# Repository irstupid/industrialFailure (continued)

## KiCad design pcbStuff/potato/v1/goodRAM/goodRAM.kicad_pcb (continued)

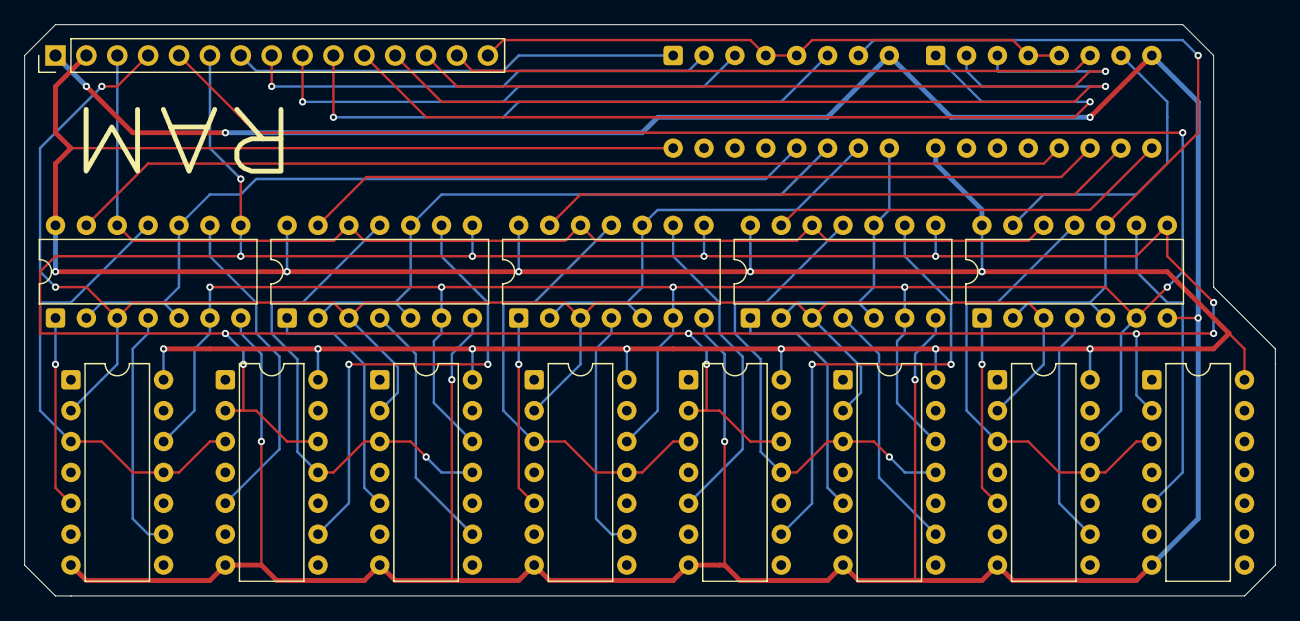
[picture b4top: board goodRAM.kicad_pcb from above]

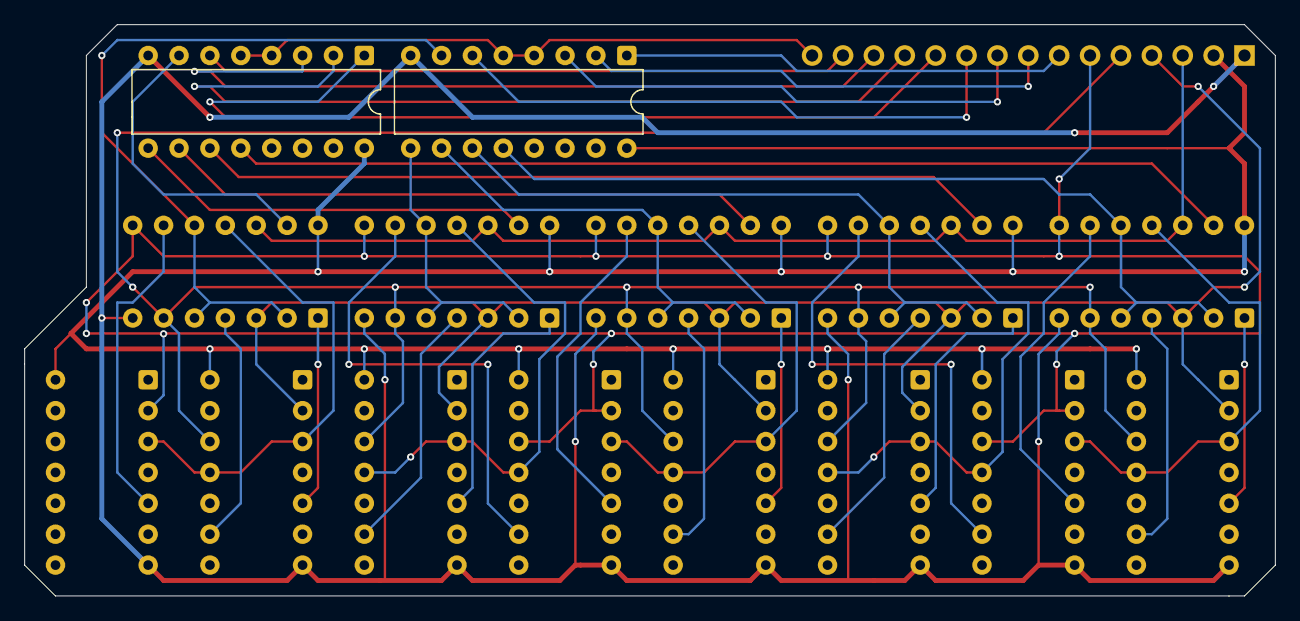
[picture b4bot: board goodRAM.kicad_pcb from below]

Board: 2 copper layers, 102.9 x 47.0 mm, 16 parts (2 on the bottom side), 45 nets.

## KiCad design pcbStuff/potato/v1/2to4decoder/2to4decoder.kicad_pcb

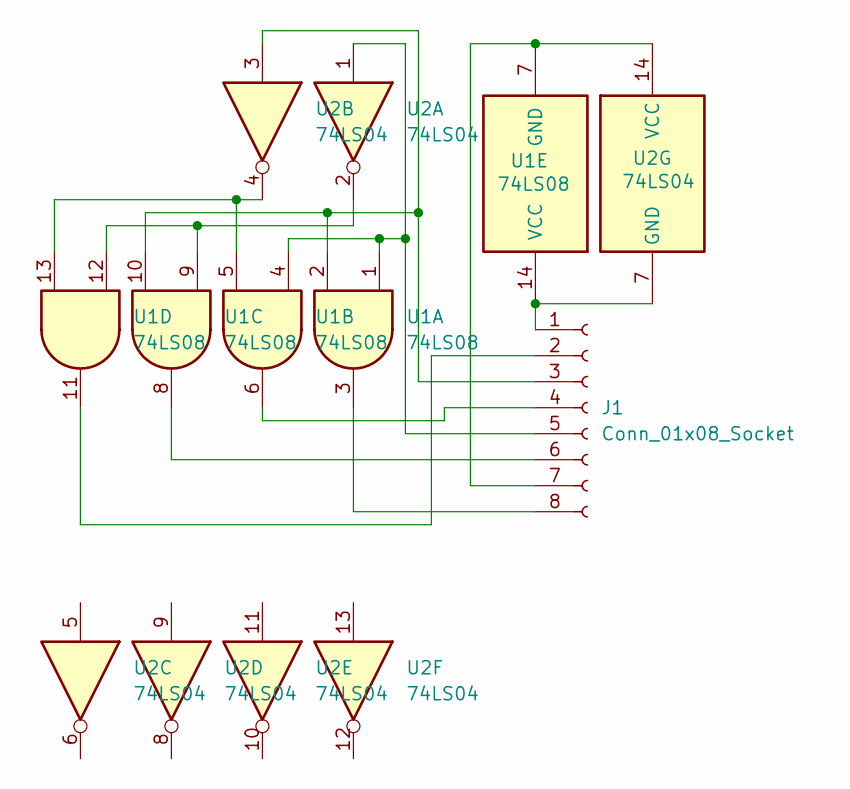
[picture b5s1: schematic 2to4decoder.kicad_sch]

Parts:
J1: Conn_01x08_Socket; PinSocket_2x04_P2.54mm_Horizontal
U1: 74LS08; DIP-14_W7.62mm
U2: 74LS04; DIP-14_W7.62mm

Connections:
unnamed: J1.1, U1.14 (VCC), U2.7 (GND)
unnamed: J1.2, U1.11
unnamed: J1.3, U1.2, U1.10, U2.3
unnamed: J1.4, U1.6
unnamed: J1.5, U1.1, U1.4, U2.1
unnamed: J1.6, U1.8
unnamed: J1.7, U1.7 (GND), U2.14 (VCC)
unnamed: J1.8, U1.3
unnamed: U1.9, U1.12, U2.2
unnamed: U1.5, U1.13, U2.4

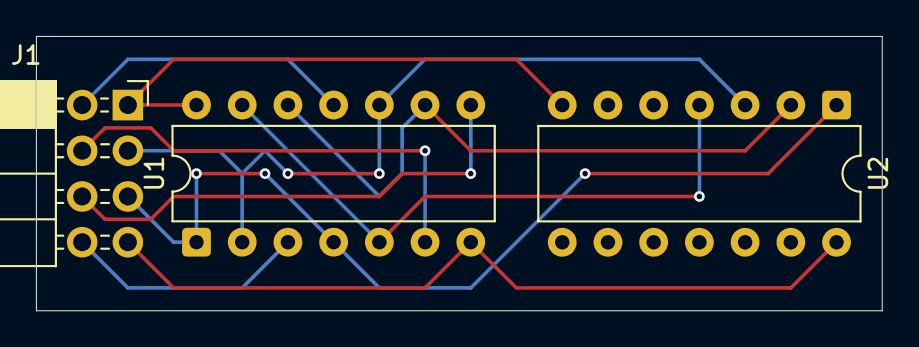
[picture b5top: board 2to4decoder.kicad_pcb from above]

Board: 2 copper layers, 47.0 x 15.2 mm, 3 parts (0 on the bottom side), 10 nets.

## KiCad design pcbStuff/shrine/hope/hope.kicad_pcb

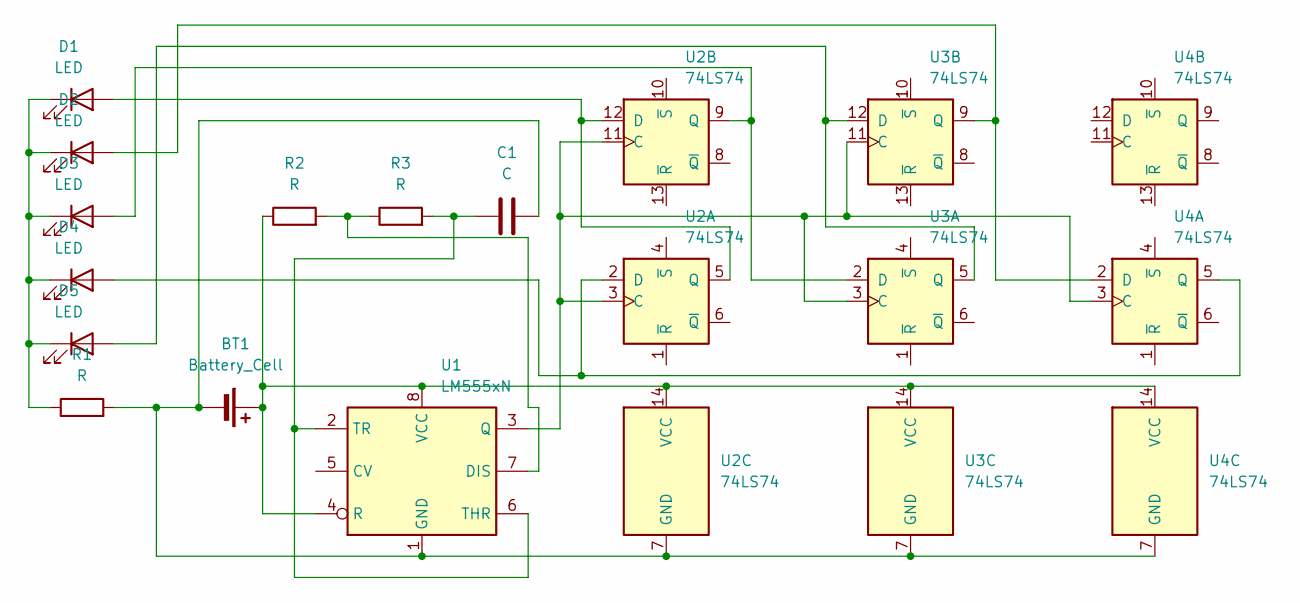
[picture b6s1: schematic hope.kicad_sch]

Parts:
BT1: Battery_Cell; BatteryHolder_Keystone_3034_1x20mm
C1: C; CP_Radial_D8.0mm_P5.00mm
D1, D2, D3, D4, D5: LED; LED_D5.0mm
R1, R2, R3: R; R_Axial_DIN0207_L6.3mm_D2.5mm_P7.62mm_Horizontal
U1: LM555xN; DIP-8_W7.62mm
U2, U3, U4: 74LS74; DIP-14_W7.62mm

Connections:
unnamed: BT1.1 (+), R2.1, U1.4 (R), U1.8 (VCC), U2.14 (VCC), U3.14 (VCC), U4.14 (VCC)
unnamed: BT1.2 (-), C1.2, R1.2, U1.1 (GND), U2.7 (GND), U3.7 (GND), U4.7 (GND)
unnamed: D1.2 (A), U2.5 (Q), U2.12 (D)
unnamed: D1.1 (K), D2.1 (K), D3.1 (K), D4.1 (K), D5.1 (K), R1.1
unnamed: D2.2 (A), U3.9 (Q), U4.2 (D)
unnamed: D3.2 (A), U2.9 (Q), U3.2 (D)
unnamed: D4.2 (A), U2.2 (D), U4.5 (Q)
unnamed: D5.2 (A), U3.5 (Q), U3.12 (D)
unnamed: R2.2, R3.1, U1.7 (DIS)
unnamed: U1.3 (Q), U2.3 (C), U2.11 (C), U3.3 (C), U3.11 (C), U4.3 (C)
unnamed: C1.1, R3.2, U1.2 (TR), U1.6 (THR)

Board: 2 copper layers, 14 parts (0 on the bottom side), 11 nets, no tracks yet.

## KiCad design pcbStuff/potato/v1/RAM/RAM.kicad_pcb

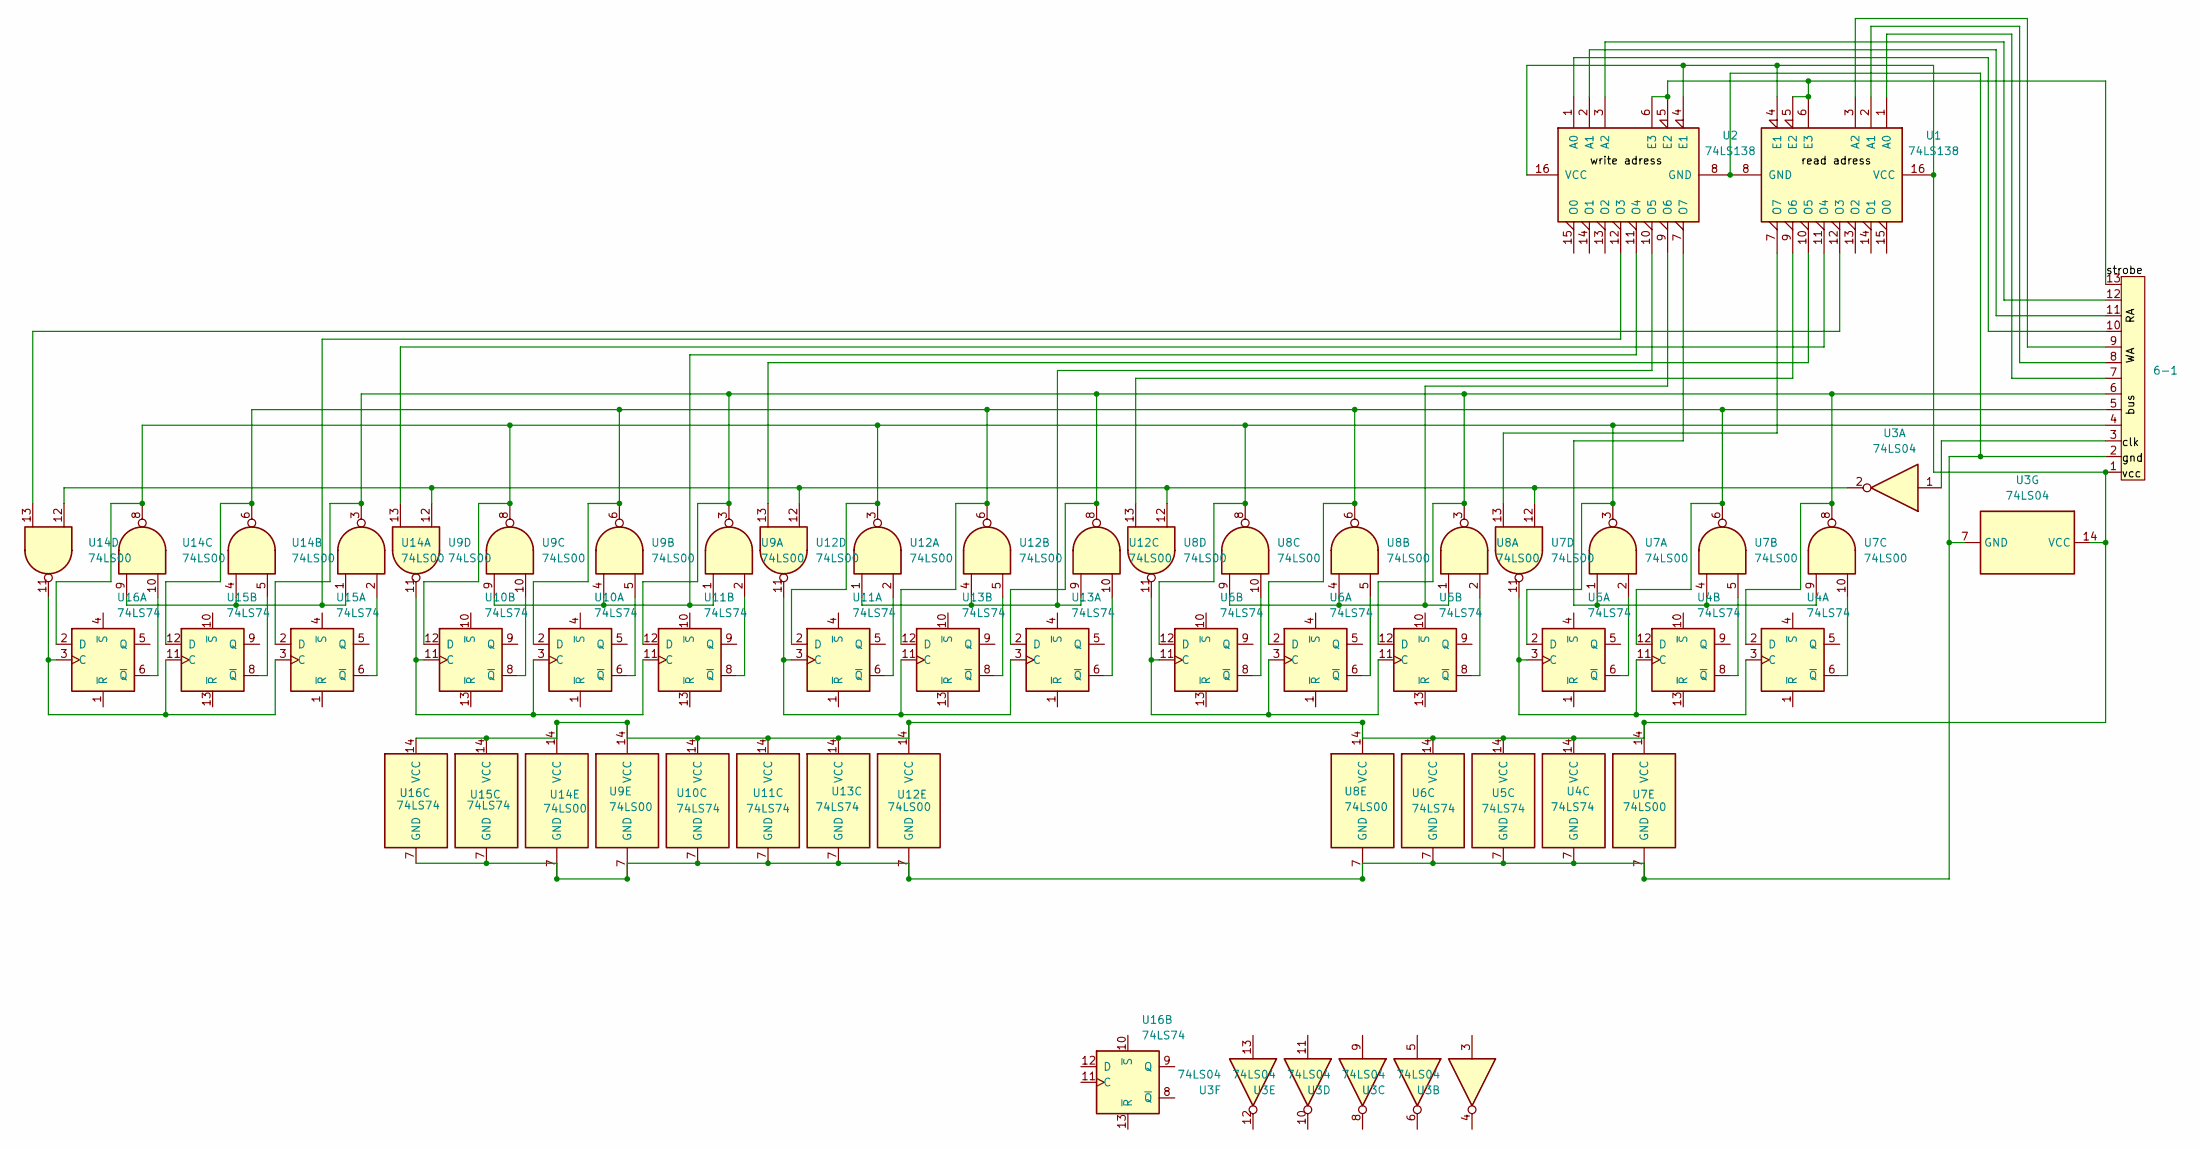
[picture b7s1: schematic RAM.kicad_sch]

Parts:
6-1: 6-7Connector
U1, U2: 74LS138; DIP-16_W7.62mm
U3: 74LS04; DIP-14_W7.62mm
U4, U5, U6, U10, U11, U13, U15, U16: 74LS74; DIP-14_W7.62mm
U7, U8, U9, U12, U14: 74LS00; DIP-14_W7.62mm

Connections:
/strobe: 6-1.13, U1.5 (E2), U1.6 (E3), U2.5 (E2), U2.6 (E3)
unnamed: 6-1.3, U3.1
unnamed: 6-1.7, U1.1 (A0)
unnamed: 6-1.8, U1.2 (A1)
unnamed: 6-1.9, U1.3 (A2)
unnamed: 6-1.1, U1.4 (E1), U1.16 (VCC), U2.4 (E1), U2.16 (VCC), U3.14 (VCC), U4.14 (VCC), U5.14 (VCC), U6.14 (VCC), U7.14 (VCC), U8.14 (VCC), U9.14 (VCC), U10.14 (VCC), U11.14 (VCC), U12.14 (VCC), U13.14 (VCC), U14.14 (VCC), U15.14 (VCC), U16.14 (VCC)
unnamed: 6-1.2, U1.8 (GND), U2.8 (GND), U3.7 (GND), U4.7 (GND), U5.7 (GND), U6.7 (GND), U7.7 (GND), U8.7 (GND), U9.7 (GND), U10.7 (GND), U11.7 (GND), U12.7 (GND), U13.7 (GND), U14.7 (GND), U15.7 (GND), U16.7 (GND)
unnamed: U1.12 (O3), U14.13
unnamed: U1.11 (O4), U9.13
unnamed: U1.10 (O5), U12.13
unnamed: U1.9 (O6), U8.13
unnamed: U1.7 (O7), U7.13
unnamed: 6-1.10, U2.1 (A0)
unnamed: 6-1.11, U2.2 (A1)
unnamed: 6-1.12, U2.3 (A2)
unnamed: U2.12 (O3), U14.1, U14.4, U14.9
unnamed: U2.11 (O4), U9.1, U9.4, U9.9
unnamed: U2.10 (O5), U12.1, U12.4, U12.9
unnamed: U2.9 (O6), U8.1, U8.4, U8.9
unnamed: U2.7 (O7), U7.1, U7.4, U7.9
unnamed: U4.3 (C), U4.11 (C), U5.3 (C), U7.11
unnamed: U4.6 (~Q), U7.10
unnamed: U4.8 (~Q), U7.5
unnamed: U5.6 (~Q), U7.2
unnamed: U5.11 (C), U6.3 (C), U6.11 (C), U8.11
unnamed: U5.8 (~Q), U8.2
unnamed: U6.6 (~Q), U8.5
unnamed: U6.8 (~Q), U8.10
unnamed: U9.11, U10.3 (C), U10.11 (C), U11.11 (C)
unnamed: 6-1.5, U4.12 (D), U6.2 (D), U7.6, U8.6, U9.6, U10.2 (D), U12.6, U13.12 (D), U14.6, U15.12 (D)
unnamed: U9.5, U10.6 (~Q)
unnamed: 6-1.4, U5.2 (D), U6.12 (D), U7.3, U8.8, U9.8, U10.12 (D), U11.2 (D), U12.3, U14.8, U16.2 (D)
unnamed: U9.10, U10.8 (~Q)
unnamed: U11.3 (C), U12.11, U13.3 (C), U13.11 (C)
unnamed: U11.6 (~Q), U12.2
unnamed: 6-1.6, U4.2 (D), U5.12 (D), U7.8, U8.3, U9.3, U11.12 (D), U12.8, U13.2 (D), U14.3, U15.2 (D)
unnamed: U9.2, U11.8 (~Q)
unnamed: U3.2, U7.12, U8.12, U9.12, U12.12, U14.12
unnamed: U12.10, U13.6 (~Q)
unnamed: U12.5, U13.8 (~Q)
unnamed: U14.11, U15.3 (C), U15.11 (C), U16.3 (C)
unnamed: U14.2, U15.6 (~Q)
unnamed: U14.5, U15.8 (~Q)
unnamed: U14.10, U16.6 (~Q)

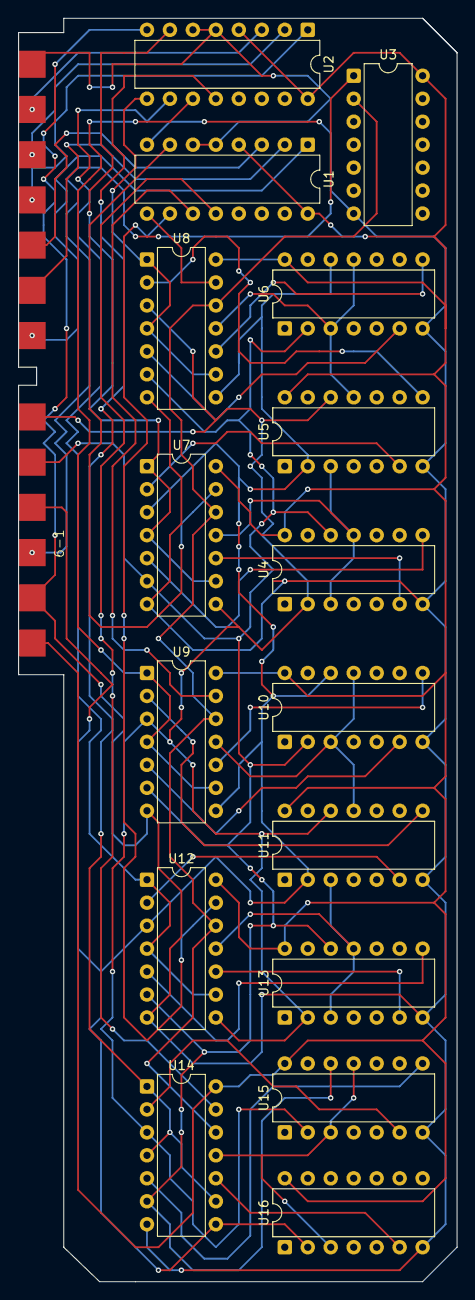
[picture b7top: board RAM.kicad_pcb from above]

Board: 2 copper layers, 48.5 x 139.6 mm, 17 parts (0 on the bottom side), 44 nets.

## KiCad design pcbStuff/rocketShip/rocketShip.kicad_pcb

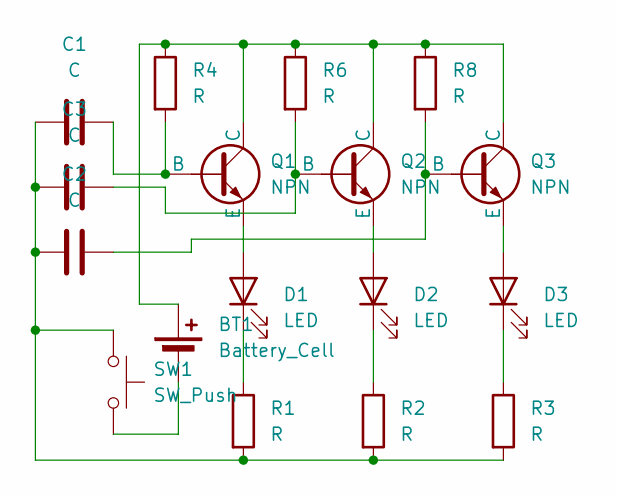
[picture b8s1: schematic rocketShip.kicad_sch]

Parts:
BT1: Battery_Cell; BatteryHolder_Keystone_3034_1x20mm
C1, C2, C3: C; CP_Radial_D8.0mm_P5.00mm
D1, D2, D3: LED; LED_D5.0mm
Q1, Q2, Q3: NPN; TO-92L_HandSolder
R1, R2, R3, R4, R6, R8: R; R_Axial_DIN0207_L6.3mm_D2.5mm_P7.62mm_Horizontal
SW1: SW_Push; SW_PUSH_6mm

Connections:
unnamed: BT1.1 (+), Q1.1 (C), Q2.1 (C), Q3.1 (C), R4.1, R6.1, R8.1
unnamed: BT1.2 (-), SW1.2
unnamed: C1.1, C2.1, C3.1, R1.2, R2.2, R3.2, SW1.1
unnamed: D1.2 (A), Q1.3 (E)
unnamed: D1.1 (K), R1.1
unnamed: D2.2 (A), Q2.3 (E)
unnamed: D2.1 (K), R2.1
unnamed: D3.2 (A), Q3.3 (E)
unnamed: D3.1 (K), R3.1
unnamed: C1.2, Q1.2 (B), R4.2
unnamed: C3.2, Q2.2 (B), R6.2
unnamed: C2.2, Q3.2 (B), R8.2

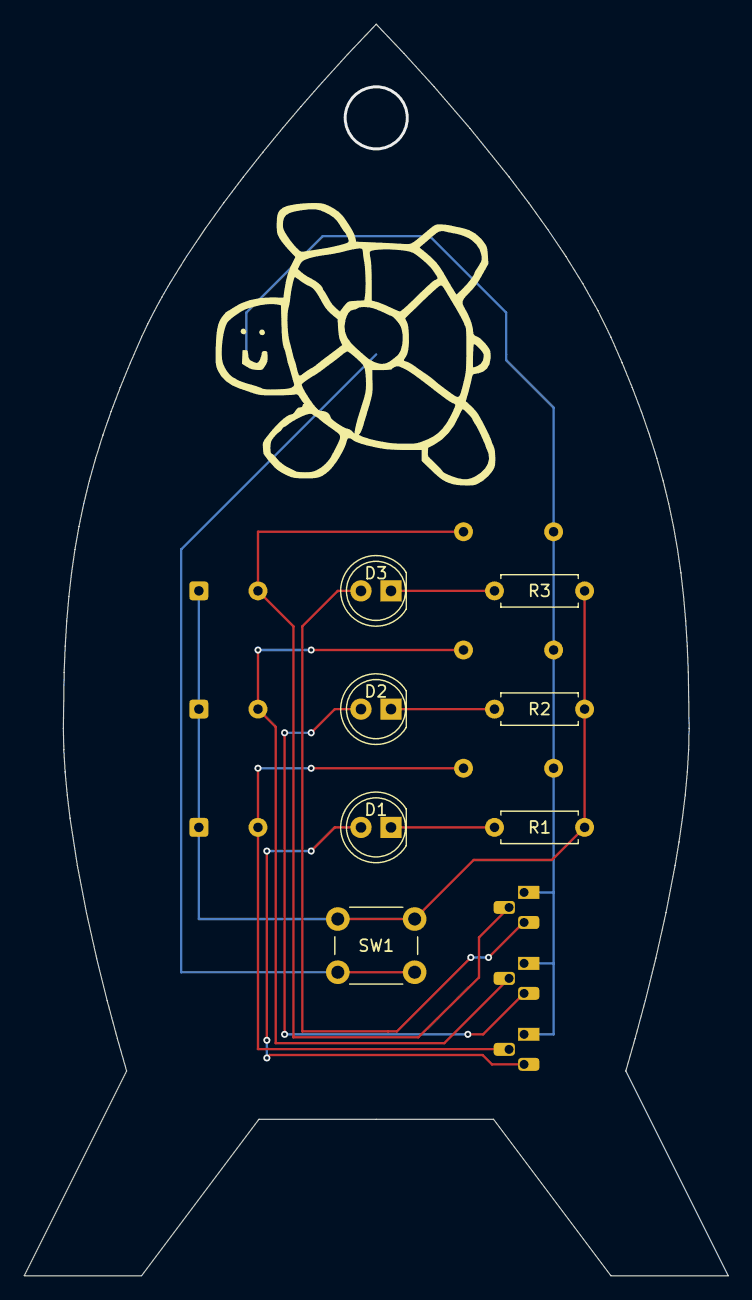
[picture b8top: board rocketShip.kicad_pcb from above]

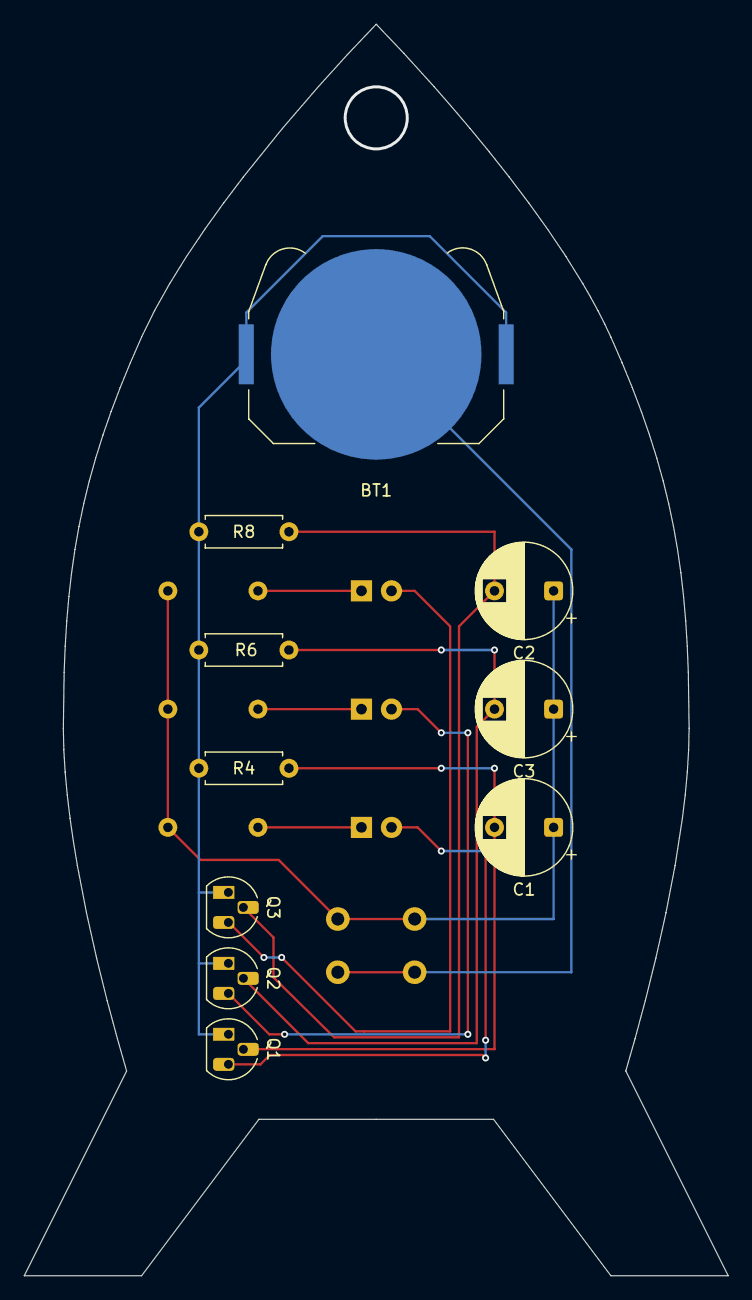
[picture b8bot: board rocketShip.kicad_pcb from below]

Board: 2 copper layers, 59.5 x 105.8 mm, 17 parts (10 on the bottom side), 12 nets.

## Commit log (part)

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2023-12-13 weee yaya i haps ohh ho
2024-01-03 it can dash now!
2024-01-03 tweked some stuff
2024-01-08 path is now an array
2024-01-08 YOU CAN MAKE ARRAY ARRAYS?
2024-01-09 enemy stuff
2024-01-09 timeing
2024-01-09 towers and shit
2024-01-10 projectiles exist, but cant spawn
2024-01-10 framework for projectile spawning
2024-01-12 harrpoon lagoon exists
2024-01-15 the pew pew go shoot shoot
2024-01-16 Revert "the pew pew go shoot shoot"
    This reverts commit dc1bf04c274e34d1b9965fe62ec8010cf479e93e.
2024-01-16 Revert "Revert "the pew pew go shoot shoot""
    This reverts commit 8c68da690649ca4615d18f1dd677aeaffeb41f41.
2024-01-18 the thig go cooooooooooool now
2024-01-18 waluigi
2024-01-24 shotty shotty pew pew
2024-01-25 cool stuff
2024-02-02 yeah
2024-02-02 errr d dd dedfxdf
2024-02-08 the cool stuff yeah
2024-02-08 YEAHEYAEHYE ye
2024-02-12 AAHHAHAHAHAHH WE WE WE WA YA LIVEVEVEVVVVVVVVVVVVVV
2024-02-15 i hate everything
2024-02-20 AAAHAHAHAHHAHAHAAHAHAHAHAHHAHAHAHH PURgotory HHHHHHHHH F L O W E R
2024-02-21 GYUWUYWYUGDDSASDGYSADGSDAGSDAYUGSDAYUDSAYUG COOOKL
2024-02-22 TTTTTTHE HEHEHEH AHAHHA DDAUHHUE AGHE DAO THE YEAHB
2024-02-28 SEZURE mode noty sezur mod surzer mod no serzer mod SewrSev mod STopSezure mod
2024-03-04 i did things yeah
2024-03-05 ALOT of stuff happened
2024-03-06 iTs 11:33 help
2024-03-06 daocollBROK
2024-03-11 da Pew Powq
2024-03-11 DAsookKEETEY woork. isma hap. bacon
2024-03-11 its fucking beautiful
2024-03-12 KabUm :)
2024-03-12 yeah yeah yeah yeah yeah yeah yeah yeah yeah yeah yeah
2024-03-13 da ZIM. (the scerete was da megnetude and direerection)
2024-03-13 ha. NOISE. zapzooboomboopbonkKABUM
2024-03-13 ha missle go BURRRRRR
2024-03-13 im a man wu=ith a OPLAN
2024-03-13 i am without te indsporetanitonal jucies flowing in my herads
2024-03-13 imisdobeCoUkinhg
2024-03-14 i have become death, death, DIERENIDATOR
2024-03-18 out of the unKNOWOWUW. (intense whispering)
2024-03-18 farther out of the UNKNOWENOEEUWU
2024-03-18 and i ned go Neow. boys
2024-03-20 he. he. he. TATATKOYEAH AND SYUFF ye
2024-03-21 many smnow mean ther are bow THEY LOBG FOR THE BLOD OF MAN< FOR THEYU ARE DEPRIVED OF SENSELSE ATE BITRDSH help
2024-03-25 nowtheColors go WOOOOO
2024-04-02 now ye SCRUE
2024-04-04 i nokwn how to save to thje JSON now i hopy YEY!
2024-04-08 yeh sol eclispes i want to summon a demoin
2024-04-09 the funy colors make me se god
2024-04-12 thwe siz eis now sizxe ghat fits YEYE
2024-04-15 i whea went through 5the five stages dfo greif THEN ADDED A 6th
2024-04-18 welp, i made no progress today
2024-04-22 ah eh oh oeoeoepoegaS whya sno woprks a and SEIXERS
2024-04-24 atgasasdasda chaong of commminf
2024-04-24 AHAHAHAHHAHAHAH picerytyrres AHAHHAHAHA
2024-04-25 FEUTRE IAN PLEAS FIX DE ARROY FLIPY THINGENY OHHHHHHHHNAEAES
2024-04-27 hahah BONK
2024-04-27 new chromeecool effecto. not shure liek/. moke din
2024-04-27 i hove decoided YES. ME DO THE LIKEY THINGEYR YEAH
2024-04-29 do it do be works on de arceodo boxies?
2024-04-29 i dont want to fix the text right now
2024-04-29 me no like polish
2024-05-01 i live in constant fear
2024-05-01 the squares do be marching
2024-05-01 now ytou do be also the marching
2024-05-02 that is enough oppening portals into hell for today :)
2024-05-02 bro 9i just dscover another circle
2024-05-02 blonkey slonkey
2024-05-02 i hap
2024-05-06 ha, de ball go WoooWOooWoo bu in tno no work
2024-05-06 now there ye
2024-05-06 i dont wat to do this anymore
2024-05-09 now there are tiles
2024-05-13 ha MNAT DO DA BOUL
2024-05-14 no there be stifu. i like god
2024-05-14 the smothest fucking criminal alive
2024-05-14 impending doom approches
2024-05-15 oh no, so it begoins
2024-05-15 oh no, da dubbeugging begens
2024-05-15 the gibles no no be locking :)
2024-05-15 ATNT molment
2024-05-15 well the lasers are not broken but the snowmen are
2024-05-16 now it is (almost) done
2024-05-16 had two thinsg to do, did neither :)
2024-05-20 AHHHHHHHHHHH why. like why. why the fuck do i do this to myself UGHHHHHHHHHHHH
2024-05-22 its black
2024-05-22 this score wipe officially marks strange place 1.0!
2024-05-22 smthing worng i can feel it
2024-05-28 YOU REMBERY PUSH SUMMBY
2024-05-30 tiggywogitry
2024-05-30 i Hate everything (exposicelllity the collideringersed)
2024-05-30 you can not touch left wall
2024-06-04 meta BALLS (the testicals understand the matrix)
2024-06-04 *hevily autonuned* RaInBOw BalLS
2024-06-04 well i changed it now. me no no no if better or no n o better
2024-06-04 wo the fing bux
2024-06-05 the thing is worky but not coyite worky. mango
2024-06-08 augh
2024-06-08 well it does something
2024-06-09 Revert "i cant do this"
    This reverts commit 3bc866c6859d9791177a9ab7477c49a2fcbfa077.
2024-06-09 i can do this
2024-06-09 particles. lots of them
2024-06-09 roses are red violets are blue i have the 800 px version of rick astleys shoe
2024-06-09 pleased to meat you
2024-06-09 allenengse
2024-06-10 passing gas
2024-06-11 cooked some awsome soup
2024-06-17 cooler particles now
2024-06-18 gay tomato (onoly took mr 3 tries)
2024-06-20 i hope this works with my iother stuff
2024-06-21 thingeyse
2024-07-02 artistic pain
2024-07-24 robots is pain
2024-07-26 rombey
2024-07-26 kabum
2024-07-29 godeyo no no workey
2024-07-30 "he's so emotional"
2024-08-07 expurt
2024-08-18 i dont need sleep i need program
2024-08-18 done?
2024-08-18 BANGER
2024-08-26 i hope it exported correctaly
2024-08-27 inharitence
2024-08-28 i aint doin no of dat shit
2024-08-28 focking chaeting w2ittle bwats
2024-08-28 expert
2024-08-30 git.ignoreMySketchySucrityAndFuckkingLetMeMakeAGithubAcount
2024-09-02 bealt werk
2024-09-04 it be kinda work
2024-09-06 ctrl a + deleat
2024-09-06 backwards crosshair
2024-09-10 shooty shooty aim aim
2024-09-11 blackl bor
2024-09-11 good good yes yes
2024-09-11 wow i nde be don
2024-09-12 it is not gay
2024-09-12 turnally correct
2024-09-17 arcode
2024-09-17 Pirating Jimbo
    Set up the Gradle Build for Shooter Robot called Jimbo.
2024-09-17 Driving ARGGGGGG
    Set up Drive Constants for the initial robot, but its Hardware Ids still need to match for code and robot.
2024-09-17 yippity yappity yay he hooooooooooooo
2024-09-17 Revert "Merge branch 'master' of https://git.lindblom.tech/irbrost/BrostIan2023"
    This reverts commit d40ec6e3abf6a03e11248ff66dab4b44a17eef94, reversing
    changes made to fcef8da192b0f79fe27d7ebf78d0c28684087590.
2024-09-17 Revert "yippity yappity yay he hooooooooooooo"
    This reverts commit fcef8da192b0f79fe27d7ebf78d0c28684087590.
2024-09-17 DO YOU WANT A B A N A N A
2024-09-18 Dead Wheels Chicanery
    Attempting to set up Dead Wheels for robot, yay
2024-09-18 Hardware ID fixing
    Fixed hardware Id's, allowing the robot to move correctly forward, backwards, and strafing.
2024-09-20 Dead Wheels Vanquished
    Completed the Dead Wheels tuning section for Jimbo by tuning the Lateral Distance of the robot.
2024-09-20 suberstoff
2024-09-26 in the sprites (get squished nerd)
2024-10-04 game loops (taste cerial)
2024-10-04 i dont want to die
2024-10-04 flower go pew pew
2024-10-11 the tomatos de be snipping
2024-10-16 i hope it saved
2024-10-16 nowth e pad key
2024-10-16 stop camping !1!!!1!
2024-10-16 hello darkness my old freind
2024-10-23 proboly somthing
2024-11-05 maybe i should change that
2024-11-08 spoon feeding
2024-11-14 i am a tired
2024-11-15 not yet death note
2024-12-06 the density shmensity propencity
2024-12-16 robit
2024-12-16 playolayer
2024-12-16 awall
2024-12-16 sdasda
2024-12-16 getting there and falling down
2024-12-17 my journey here has come to an end.
    i have reached the limits of what processing can do. i must move on. oh noes
2024-12-17 the end/begining of an eara
2024-12-18 packagioes
2024-12-20 HGOLY FUCKING SHIT IT WORKS WOOOOOOOOOOOOOOOOOOOOOOOOO
2024-12-20 why must you motivate me
2025-01-05 IMADETHEWATERMELONMOVEHOLYSHIT
2025-01-05 good things comming
2025-01-08 game loop shenanigans
2025-01-10 i figured it out but it dosent work (yet)
2025-01-15 sdsfghjykukeryswatfx
2025-01-21 my brain hurts
2025-01-26 please god merge properly
2025-01-27 certifiably wack ass hops
2025-01-28 i dont feel like tackling that right now
2025-01-28 4520 CHANGED FILES?!
    jk i literly just changed the names of everything :)
2025-02-03 wholpe
2025-02-03 wonder whole
2025-02-11 asdjasd
2025-02-12 morn'n
2025-02-13 its the day
2025-02-14 whas da fuck
2025-02-14 W keyboard
    bro i gotta get me one of these
2025-02-15 very cool? very cool.
2025-02-18 gotta go fasht
2025-02-18 jonas :)
2025-02-18 gogg
2025-02-19 BE ON TASK
2025-02-21 stupeder than me
2025-02-24 failure
2025-02-24 HOLY SHIT BANDLE MROT
2025-02-26 minor whoopsies
2025-03-02 maybe please dont kill me :)
2025-03-05 help
2025-03-07 some stuff
2025-03-11 fuck you apple
2025-03-11 something something
2025-03-11 the writer
2025-03-11 actually peak java programming right here
2025-03-11 at leaste my topology isent that bad
2025-03-12 oh shit i got stuff to do
2025-03-12 why no work?
2025-03-14 MEGATRON
2025-03-15 oh noes
2025-03-16 they be forcin me to play bord games with them ;(
2025-03-18 peace
2025-03-18 ultimate turtle garrafe
2025-03-21 redirect
2025-04-04 ya momma
2025-04-08 fuckle my buckle
2025-04-09 they be bad people
2025-04-12 the princess of productivity
2025-04-13 slightly ardino
2025-04-13 the riddence of the demon
2025-04-14 wazziz
2025-04-15 couldent thinn of anything clever
2025-04-15 pasdo
2025-04-17 ok thats cool
2025-04-22 i cannot draw i am in pain
2025-04-22 hope this dosent fuck anything up
2025-04-24 please dont break
2025-04-25 "sound wiil be easy" - famous last words
2025-04-25 ????????? ok fuck me i guess
2025-04-27 arteist
2025-05-02 i dont wanna
2025-05-02 thangs chat gpt
2025-05-06 the JPNGifacation
2025-05-07 maybe cool (not you)
2025-05-07 ya know what, fuck you chat gpt
2025-05-16 gud jorb
2025-05-19 gud me thinks
2025-05-20 ? ? ? * ? (its the song)
2025-05-20 quick fast and in a hurry
2025-05-21 my commits are actually crazy
2025-05-21 wander arround
2025-05-23 goooooooo
2025-05-28 1234567890 UI DESIGHN IS PAIN
2025-05-28 we2aqeukhijsdfvkhijudsfgv
2025-05-29 ishould PROBNOLY REALLY MAYBE CALL MAMA NOW
2025-05-30 heeeeeeeeeeell yeah that be some smooooooooooth movement
2025-06-05 he thought i couldent download github desktop >:D
2025-06-06 thats fine i dident want to play with you anyway
2025-06-06 daym thats complicated
2025-06-10 im not even gonna write a log for that
2025-06-30 *whisper* secret commit
2025-06-30 also hidden commit
2025-07-12 it might not actually work
2025-08-15 mostly cinema
2025-08-23 a return to form
2025-08-24 gergation
2025-08-24 almost forgot
2025-08-30 the dessepering man
2025-09-01 sometimes it does that
2025-09-01 new record!
2025-09-20 fucking gnu
2025-09-20 not now kitten wiskers, daddy will debug this LATAR
2025-09-21 it works!
2025-10-03 maybe should just leave that for latter
2025-10-04 look it mostly works, ok
2025-10-08 i might need to have a ponder
2025-10-22 really gots to go now
2025-10-23 maybe work???
2025-11-19 SSRI
2025-11-19 look how the massacred my boy
2025-11-19 why is it laggy?
2025-12-03 do something
2025-12-03 pain, suffering
2025-12-09 THE FUCK YOU MEAN 1.27
2025-12-10 im confused
2026-01-02 why were you there?
2026-01-02 please no ssh
2026-01-07 oh my dear god
2026-01-07 i am fucking lossing it
2026-01-09 only 5 remain
2026-01-10 2 LIttlE FUCKERS
2026-01-16 why is it impossible
2026-01-26 truly a pcb of all time
2026-01-26 math
2026-01-27 complement!
2026-01-28 im very bad
2026-01-28 DONE! ish
2026-01-28 PROGRESS FUCK YEAH
2026-01-29 holy moly progress
2026-01-29 i hate that trash
2026-01-30 motivation stocks are tanking right now
2026-01-30 double reverse progress
2026-01-31 J U I C E
2026-01-31 not doing that right now
2026-02-01 just in case part 2
2026-02-03 weakness
2026-02-04 c brain
2026-02-04 one day your sins will catch up to you
2026-02-04 progress is progress
2026-02-05 i hate myself
2026-02-05 beauty is in the eye of the beholder
2026-02-08 poor mans factorio
2026-02-22 p[iofspojasdf
2026-02-22 song
2026-02-22 fixing my relationship
2026-02-22 swerving out of the way to avoid a car crash
2026-02-22 deep rock?
2026-02-24 lights go blam
2026-03-03 gotta go fast
2026-03-04 i dont trust you with my c files microsoft
2026-03-04 gotta take breaks
2026-03-05 fable foo
2026-03-19 wawawewe
2026-04-10 removed some unececssary code
2026-04-17 balls
2026-05-06 test
